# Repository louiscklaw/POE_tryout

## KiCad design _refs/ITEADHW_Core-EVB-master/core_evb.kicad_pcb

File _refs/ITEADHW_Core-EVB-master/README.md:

Core-EVB
================

    History:
    V1.4
    Add the auto reset circuit.
    V1.3
    Improve the Mic and speaker circuit.
    Replace HLF-W12 to HLF-W15.
    Add the PWM and Power function in FPC.
    Fix the RJ45 LED bug.
    Fix some stablity issues.
    V1.2
    First release.

================

Core EVB is a customized evaluation board for ITEAD Core AW204x, which pinouts the functional pins of AW204x to the corresponding physical interface such as USB ports, SD card slot Ethernet port etc. Moreover, Core EVB provides a 40 pins interface that is compatible with RPI B+, which will help developers utilize the existing Add-on more easily.

Common A20 development boards in the market only provide Line-in/Line-out interface so that they can't drive a loudspeaker directly. However, we add power amplifier so that it can drive 4ohm or 8ohm speaker easily.

You can get more information about this project on our wiki:
http://wiki.iteadstudio.com/Core_EVB

Copyright © ITEAD Studio

Lcisense: GPL V3

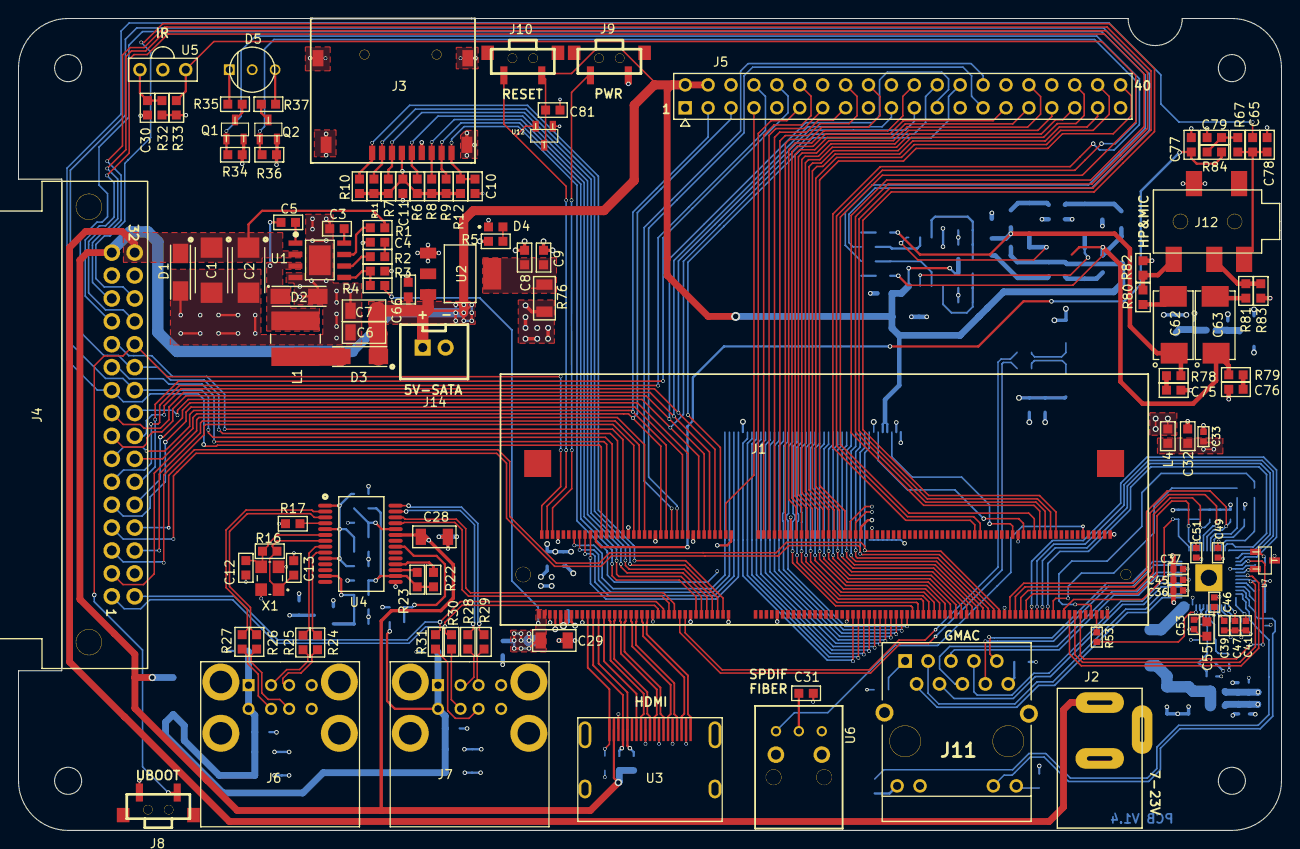
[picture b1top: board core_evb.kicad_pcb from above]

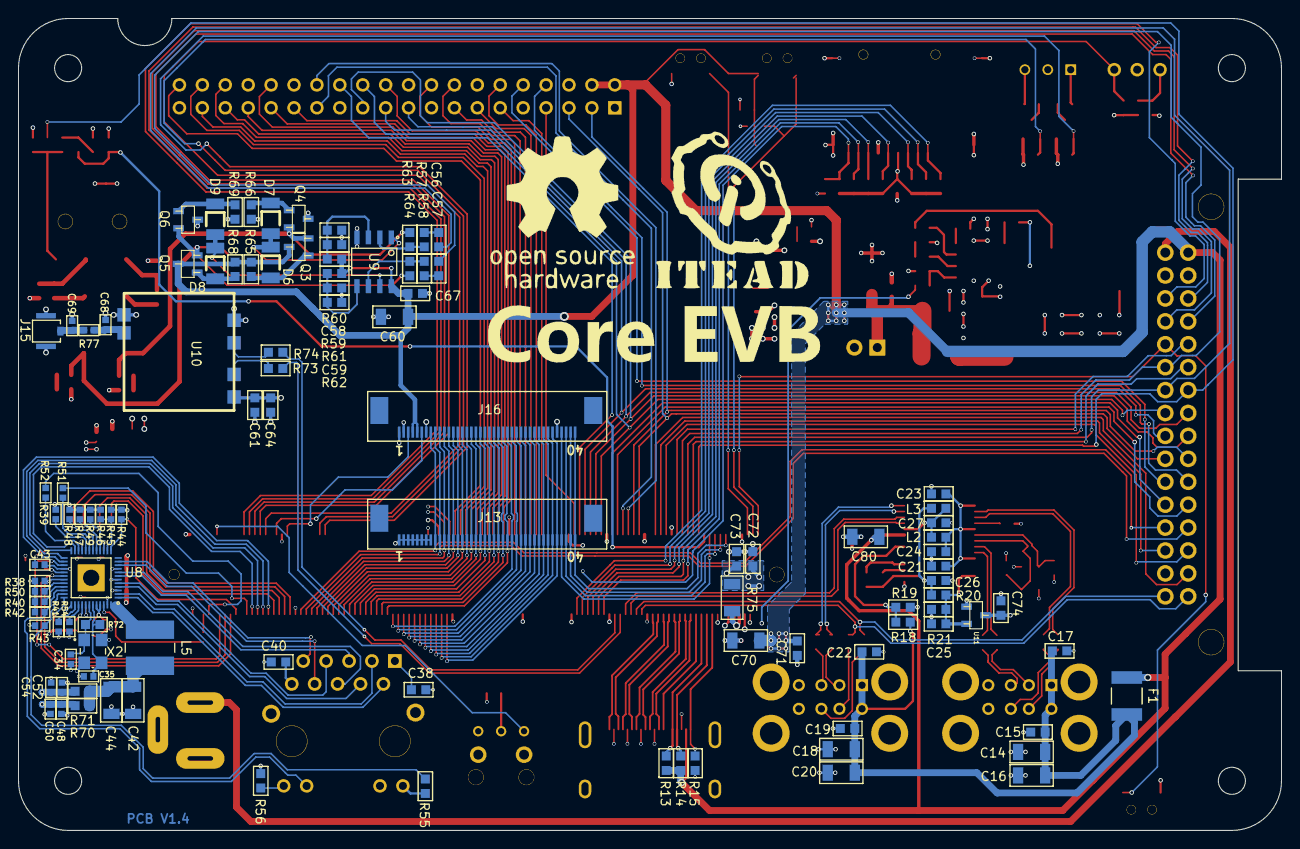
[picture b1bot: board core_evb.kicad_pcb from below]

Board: 4 copper layers, 140.0 x 90.0 mm, 216 parts (105 on the bottom side), 225 nets.

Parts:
C1, C2: 22uF/C6031-28; CAPMP6032X280
C3, C9, C10, C11, C15, C17, C19, C21, C22, C23, C24, C26, C27, C38, C40, C61, C67, C71, C74, C75, C76, C81: 100nF/0603; STD0603
C4: 3.9nF/0603; STD0603
C5: 10nF/0603; STD0603
C6, C7, C14, C16, C18, C20, C28, C29, C42, C44, C60, C70, C80: 22uF/1206; STD1206
C8, C32, C55, C56, C57, C58, C59, C64, C66, C72, C73, C77, C79: 10uF/0603; STD0603
C12, C13: 12pF/0603; STD0603
C25, C65: 1uF/0603; STD0603
C30, C31: 4.7uF/0603; STD0603
C33, C36, C37, C39, C41, C43, C45, C46, C47, C48, C49, C50, C51, C52, C53, C54: 100nF/0402; STD0402
C34, C35: 22pF/0402; STD0402
C62, C63: 470uF/E7343-43; CAPMP7343X430
C68, C69: NC/0402; STD0402
C78: NC/10pF/0603; STD0603
D1, D2, D3: 1N5819; DIOM5025X231
D4: GREEN/0603; LED0603
D5: 3PLED
D6, D7, D8, D9: 1N4148; diomelf3517
F1: 500mA/1812; STD1812
J1: DIMM204; TYCO-2-2013022
J2: DC_SOCKET
J3: MICRO-SD-TF01
J4: CON-16X2; 9001-35321C00A
J5: CON_2X20; ZCZ254-2X20
J6, J7: USB_B_F_X2
J8, J9, J10: S_1P1T; TS-017
J11: RJ45-HR911130C; RJ45-HY911130C
J12: PJ-327F
J13, J16: CON_1X40; fpc40_0_5mm_up
J14: CON-1X2; XH254-2P
J15: IPX; ipx
L1: 10uH/5.2X5.2/3A; INDC5252X450N
L2, L3, L4: 100R/100MHZ/0603; STD0603
L5: 4.7uH/5.2X5.2; INDC5252X450N
Q1, Q2: 2N7002; sot_23
Q3, Q5: SI2302; sot_23
Q4, Q6: SI2301; sot_23
R1, R63, R64: 100KR/0603; STD0603
R2: 6.8KR/0603; STD0603
R3, R6, R7, R8, R9, R10, R11, R12, R13, R14, R15, R18, R19, R20, R22, R23, R33, R59, R60, R61, R62, R65, R66, R68, R69, R82, R83: 10KR/0603; STD0603
R4: 44.2KR/0603; STD0603
R5, R34, R35, R36, R37: 1KR/0603; STD0603
R16, R72: 1MR/0603; STD0603
R17: 680R/0603; STD0603
R21: NC/10KR/0603; STD0603
R24, R25, R26, R27, R28, R29, R30, R31, R73, R74, R78, R79: 22R/0603; STD0603
R32, R84: 100R/0603; STD0603
R38: 1.5KR/0402; STD0402
R39, R40, R42, R43, R44, R46, R47, R48, R49, R50: 4.7KR/0402; STD0402
R41, R51, R52, R53, R77: 0R/0402; STD0402
R45: NC/4.7KR/0402; STD0402
R54: 2.49KR/0402; STD0402
R55, R56: 510R/0603; STD0603
R57, R58: 20KR/0603; STD0603
R67: 2KR/0603; STD0603
R70, R71, R80, R81: 0R/0603; STD0603
R75: 0R/1206; STD1206
R76: NC/0R/1206; STD1206
U1: MP2307; SOP127P600X150-8T330X240
U2: LM1117; SOT-223
U3: HDMI; hdmi-001-05
U4: GL850G; SSOP-28
U5: HS0038B
U6: HLT1160
U7, U11: APX809; sot_23
U8: RTL8211E; QFN40P600X600X80-49P
U9: SGM358; SOP8
U10: HLF-W12
U12: APX810; sot_23
X1: 12MHz; OSCCC250X320X100
X2: 25MHz; OSCCC250X320X100

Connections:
3V3: C11.1, C31.1, C61.1, C64.1, C72.1, C73.1, C74.1, D5.2, J3.4, J4.30, J5.1, J5.17, L4.1, R5.1, R6.1, R7.1, R8.1, R9.1, R10.1, R11.1, R12.1, R32.2, R33.2, R56.2, R75.1, R76.2, U6.2, U10.1, U11.3
5V: C6.1, C7.1, C28.1, C29.1, C60.1, C66.1, C67.1, C70.1, C71.1, C80.1, C81.1, D3.C, F1.1, J1.1, J1.3, J4.31, J5.2, J5.4, J10.1, J14.1, J16.4, J16.5, Q3.3, Q5.3, R4.2, R13.1, R14.1, R59.1, R61.1, R65.1, R68.1, U2.3, U3.18, U4.23, U9.8, U12.3
/gmac/25MI: C34.1, R72.2, U8.42, X2.1
/gmac/25MO: C35.1, R72.1, U8.43, X2.3
/gmac/ENSWREG: R41.1, U8.38
/gmac/INT#: R39.1, U8.20
/gmac/LED0: J11.13, R42.1, U8.34
/gmac/LED1: R43.1, R55.1, U8.35
/gmac/LED2: R50.1, U8.32
/gmac/PHYRST#: U7.2, U8.29
/gmac/PMEB: R40.1, U8.33
/gmac/REGOUT: L5.1, U8.48
/speaker&mic/HPLOUT: J12.2, R80.2, R82.1
/speaker&mic/HPROUT: J12.3, R81.2, R83.1
/speaker&mic/MIC: C65.2, C78.2, J12.5, R67.2
/usb/HUBDM1: R28.2, U4.27
/usb/HUBDM2: R26.2, U4.2
/usb/HUBDM3: R24.2, U4.8
/usb/HUBDP1: R29.1, U4.28
/usb/HUBDP2: R27.1, U4.3
/usb/HUBDP3: R25.1, U4.9
/usb/HUBRST#: C25.1, R20.1, R21.2, U4.13, U11.2
/usb/HUBSEL: R23.1, U4.17
/usb/OVCUR: R18.1, R19.2, U4.21
/usb/PGANG: R22.1, U4.18
/usb/USB-AVDD: C21.1, C23.1, C24.1, L2.1, U4.1, U4.5, U4.10
/usb/USB-DVDD: C26.1, L3.1, R20.2, R22.2, R23.2, U4.16
/usb/VBUS: C14.1, C15.1, C16.1, C17.1, C18.1, C19.1, C20.1, C22.1, F1.2, J6.1, J6.5, J7.1, J7.5, R18.2
AVDD10: C36.1, C37.1, C39.1, C48.1, C50.1, R70.2, U8.3, U8.9, U8.40
CLKIN: R53.2, U8.46
DM0: J1.45, J4.1, R30.2
DM1: J1.49, U4.25
DM2: J1.53, R73.2
DP0: J1.47, J4.2, R31.1
DP1: J1.51, U4.26
DP2: J1.55, R74.2
DVDD10: C41.1, C43.1, C52.1, C54.1, R71.2, U8.28, U8.36
EGCLKIN: J1.199, R53.1
EGTXCLK: J1.197, R52.2
EMDC: J1.189, U8.30
EMDIO: J1.191, R38.1, U8.31
ERXCLK: J1.183, R51.2
ERXD0: J1.173, R45.1, R46.1, U8.14
ERXD1: J1.171, R49.1, U8.16
ERXD2: J1.169, R47.1, U8.17
ERXD3: J1.167, R48.1, U8.18
ERXDV: J1.187, R44.1, U8.13
ETXD0: J1.181, U8.23
ETXD1: J1.179, U8.24
ETXD2: J1.177, U8.25
ETXD3: J1.175, U8.26
ETXEN: J1.193, U8.27
GND: C1.2, C2.2, C3.2, C4.2, C6.2, C7.2, C8.2, C9.2, C10.2, C11.2, C12.2, C13.2, C14.2, C15.2, C16.2, C17.2, C18.2, C19.2, C20.2, C21.2, C22.2, C23.2, C24.2, C25.2, C26.2, C27.2, C28.2, C29.2, C30.2, C31.2, C32.2, C33.2, C34.2, C35.2, C36.2, C37.2, C38.2, C39.2, C40.2, C41.2, C42.2, C43.2, C44.2, C45.2, C46.2, C47.2, C48.2, C49.2, C50.2, C51.2, C52.2, C53.2, C54.2, C55.2, C58.2, C59.2, C60.2, C61.2, C64.2, C66.2, C67.2, C68.2, C69.2, C70.2, C71.2, C72.2, C73.2, C74.2, C75.2, C76.2, C77.1, C78.1, C79.1, C80.2, C81.2, D1.A, D2.A, D4.2, J1.5, J1.7, J1.8, J1.13, J1.17, J1.34, J1.43, J1.44, J1.57, J1.58, J1.71, J1.72, J1.81, J1.86, J1.107, J1.112, J1.165, J1.170, J1.203, J1.204, J2.3, J3.6, J3.10, J3.11, J3.12, J3.13, J4.29, J5.6, J5.9, J5.14, J5.20, J5.25, J5.30, J5.34, J5.39, J6.4, J6.8, J6.9, J6.10, J6.11, J6.12, J7.4, J7.8, J7.9, J7.10, J7.11, J7.12, J8.1, J9.1, J11.12, J12.4, J13.1, J13.2, J13.3, J13.4, J13.5, J13.6, J13.7, J13.8, J14.2, J15.2, J16.1, J16.2, J16.7, J16.36, Q1.2, Q2.2, Q4.3, Q6.3, R3.2, R15.2, R17.1, R19.1, R21.1, R34.1, R36.1, R43.2, R44.2, R45.2, R54.2, R60.2, R62.2, R66.2, R69.2, R82.2, R83.2, U1.4, U1.9, U2.1, U3.2, U3.5, U3.8, U3.11, U3.17, U3.20, U3.21, U3.22, U3.23, U4.15, U5.2, U6.1, U7.1, U8.47, U8.49, U9.4, U10.4, U10.5, U11.1, U12.1, X1.2, X1.4, X2.2, X2.4
HCEC: J1.25, U3.13
HCOM: J1.32, J4.23
HHPD: J1.19, R15.1, U3.19
HPL: C56.1, J1.28, J4.20
HPR: C57.1, J1.30, J4.22
HSCL: J1.23, R13.2, U3.15
HSDA: J1.21, R14.2, U3.16
HTX0N: J1.31, U3.9
HTX0P: J1.33, U3.7
HTX1N: J1.35, U3.6
HTX1P: J1.37, U3.4
HTX2N: J1.39, U3.3
HTX2P: J1.41, U3.1
HTXCN: J1.27, U3.12
HTXCP: J1.29, U3.10
I2C1-SCL: J1.46, J4.14, J5.5
I2C1-SDA: J1.48, J4.13, J5.3
I2C2-SCL: J1.50, J5.28
I2C2-SDA: J1.52, J5.27
I2S-BCLK: J1.180, J4.26
I2S-DOUT: J1.184, J4.28
I2S-LRCLK: J1.182, J4.27
I2S-MCLK: J1.178, J4.25
IR0-RX: J1.176, R33.1, U5.1
LCD0_CLK: J1.157, J13.12, J16.11
LCD0_D0: J1.109, J13.36, J16.35
LCD0_D1: J1.111, J13.35, J16.34
LCD0_D2: J1.113, J13.34, J16.33
LCD0_D3: J1.115, J13.33, J16.32
LCD0_D4: J1.117, J13.32, J16.31
LCD0_D5: J1.119, J13.31, J16.30
LCD0_D6: J1.121, J13.30, J16.29
LCD0_D7: J1.123, J13.29, J16.28
LCD0_D8: J1.125, J13.28, J16.27
LCD0_D9: J1.127, J13.27, J16.26
LCD0_D10: J1.129, J13.26, J16.25
LCD0_D11: J1.131, J13.25, J16.24
LCD0_D12: J1.133, J13.24, J16.23
LCD0_D13: J1.135, J13.23, J16.22
LCD0_D14: J1.137, J13.22, J16.21
LCD0_D15: J1.139, J13.21, J16.20
LCD0_D16: J1.141, J13.20, J16.19
LCD0_D17: J1.143, J13.19, J16.18
LCD0_D18: J1.145, J13.18, J16.17
LCD0_D19: J1.147, J13.17, J16.16
LCD0_D20: J1.149, J13.16, J16.15
LCD0_D21: J1.151, J13.15, J16.14
LCD0_D22: J1.153, J13.14, J16.13
LCD0_D23: J1.155, J13.13, J16.12
LCD0_DE: J1.159, J13.11, J16.10
LCD0_HSYNC: J1.161, J4.7, J13.10, J16.9
LCD0_VSYNC: J1.163, J4.8, J13.9, J16.8
LINL: C65.1, J1.24, J4.19
LINR: J1.26, J4.21
MDI0+: J11.2, U8.1
MDI0-: J11.3, U8.2
MDI1+: J11.4, U8.4
MDI1-: J11.7, U8.5
MDI2+: J11.5, U8.7
MDI2-: J11.6, U8.8
MDI3+: J11.8, U8.10
MDI3-: J11.9, U8.11
unnamed: J1.9, J1.11, R75.2
unnamed: R3.1, R4.1, U1.5
unnamed: C3.1, U1.8
unnamed: C5.1, U1.1
unnamed: R2.1, U1.6
unnamed: C5.2, D2.C, L1.1, U1.3
unnamed: R1.2, U1.7
unnamed: C4.1, R2.2
unnamed: D4.1, R5.2
unnamed: C8.1, C9.1, R76.1, U2.4
unnamed: D3.A, L1.2
unnamed: J6.6, R26.1
unnamed: J6.7, R27.2
unnamed: J7.2, R28.1
unnamed: J6.3, R25.2
unnamed: J6.2, R24.1
unnamed: J7.3, R29.2
unnamed: J7.6, R30.1
unnamed: J7.7, R31.2
unnamed: C69.1, J15.1, R77.1
unnamed: C68.1, R77.2, U10.6
unnamed: R74.1, U10.3
unnamed: R73.1, U10.2
unnamed: R17.2, U4.4
unnamed: C12.1, R16.1, U4.6, X1.3
unnamed: C13.1, R16.2, U4.7, X1.1
unnamed: Q1.3, R35.1
unnamed: D5.1, R35.2
unnamed: D5.3, R37.2
unnamed: Q2.3, R37.1
unnamed: C30.1, R32.1, U5.3
unnamed: C42.1, C44.1, L5.2, R70.1, R71.1
unnamed: C38.1, J11.1
unnamed: R54.1, U8.39
unnamed: C40.1, J11.10
unnamed: J11.11, R55.2
unnamed: J11.14, R56.1
unnamed: D8.A, Q5.1, R68.2
unnamed: D9.C, Q6.1, R69.1
unnamed: D8.C, D9.A, U9.7
unnamed: D7.C, Q4.1, R66.1
unnamed: D6.C, D7.A, U9.1
unnamed: C62.2, R80.1
unnamed: C63.2, R81.1
unnamed: C76.1, R79.2
unnamed: C75.1, R78.2
unnamed: C62.1, Q3.2, Q4.2, R63.2, R78.1
unnamed: C79.2, R67.1, R84.2
unnamed: C63.1, Q5.2, Q6.2, R64.2, R79.1
unnamed: D6.A, Q3.1, R65.2
unnamed: C59.1, R61.2, R62.1, U9.5
unnamed: C57.2, R58.1
unnamed: C56.2, R57.1
unnamed: R57.2, R63.1, U9.2
unnamed: C58.1, R59.2, R60.1, U9.3
unnamed: R58.2, R64.1, U9.6
PB2: J1.172, J16.6
PB13: J1.194, U6.3
PB22: J1.54, J4.9
PB23: J1.56, J4.10
PG0: J1.88, J5.22
PG1: J1.90, J5.29
PG2: J1.92, J5.31
PG3: J1.94, J5.32
PG4: J1.96, J5.33
PG5: J1.98, J5.35
PG6: J1.100, J5.36
PG7: J1.102, J5.37
PG8: J1.104, J5.38
PG9: J1.106, J5.40
PG10: J1.108, J4.11, J5.8
PG11: J1.110, J4.12, J5.10
PH1: C10.1, J1.116, J3.9, R12.2
PH20: J1.154, Q1.1, R34.2
PH21: J1.156, Q2.1, R36.2
PH27: J1.168, J16.3
PI10: J1.60, J4.18, J5.24
PI11: J1.62, J4.15, J5.23
PI12: J1.64, J4.17, J5.19
PI13: J1.66, J4.16, J5.21
PI14: J1.68, J5.26
PI15: J1.70, J5.7
PI16: J1.74, J5.11
PI17: J1.76, J5.12
PI18: J1.78, J5.13
PI19: J1.80, J5.15
PI20: J1.82, J5.16
PI21: J1.84, J5.18
PWR: J1.6, J9.2
RESET: J1.4, J10.2, U12.2
RXCLK: R51.1, U8.19
SD0-CLK: J1.63, J3.5, R6.2
SD0-CMD: J1.65, J3.3, R7.2
SD0-D0: J1.61, J3.7, R8.2
SD0-D1: J1.59, J3.8, R9.2
SD0-D2: J1.69, J3.1, R10.2
SD0-D3: J1.67, J3.2, R11.2
TVOUT0: J1.36, J4.5
TVOUT1: J1.38, J4.6
TVOUT2: J1.40, J4.3
TXCLK: R52.1, U8.22
UBOOT: J1.2, J4.24, J8.2
USB3V3: C27.1, L2.2, L3.2, U4.24
VDD33: C32.1, C33.1, C45.1, C46.1, C47.1, C49.1, C51.1, C53.1, C55.1, L4.2, R38.2, R39.2, R40.2, R41.2, R42.2, R46.2, R47.2, R48.2, R49.2, R50.2, U7.3, U8.6, U8.15, U8.21, U8.37, U8.41, U8.44, U8.45
VIN: C1.1, C2.1, D1.C, J2.1, J4.32, R1.1, U1.2
VMIC: C77.2, J1.22, R84.1
X1: J1.14, J13.40, J16.40
X2: J1.16, J13.39, J16.39
Y1: J1.18, J13.38, J16.38
Y2: J1.20, J13.37, J16.37

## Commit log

2018-11-25 update,
2020-05-05 ci: init travis token,
2020-05-05 ci: init travis build config,
